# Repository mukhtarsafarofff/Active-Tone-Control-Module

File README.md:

(ENG) This electronic circuit consists of a network of filters which modify the signal before it is fed to speakers, headphones or recording devices by way of an amplifier. Tone control circuit  allows listeners to adjust sound to their liking and  the high-end of your tone. This enables the listener to customize the music output with either a high level of low frequency content through bass boost, or an increased level of high frequency content through a treble boost. The TL074 IC is a high-speed JFET input single operational amplifier.

(DEU) Diese elektronische Schaltung besteht aus einem Netzwerk von Filtern,die das Signal modifizieren, bevor es über einen Verstärker an Lautsprecher, Kopfhörer oder Aufnahmegeräte weitergeleitet wird. Mit der Klangregelungsschaltung können Zuhörer den Klang nach ihren Wünschen und den Höhen Ihres Tons anpassen.

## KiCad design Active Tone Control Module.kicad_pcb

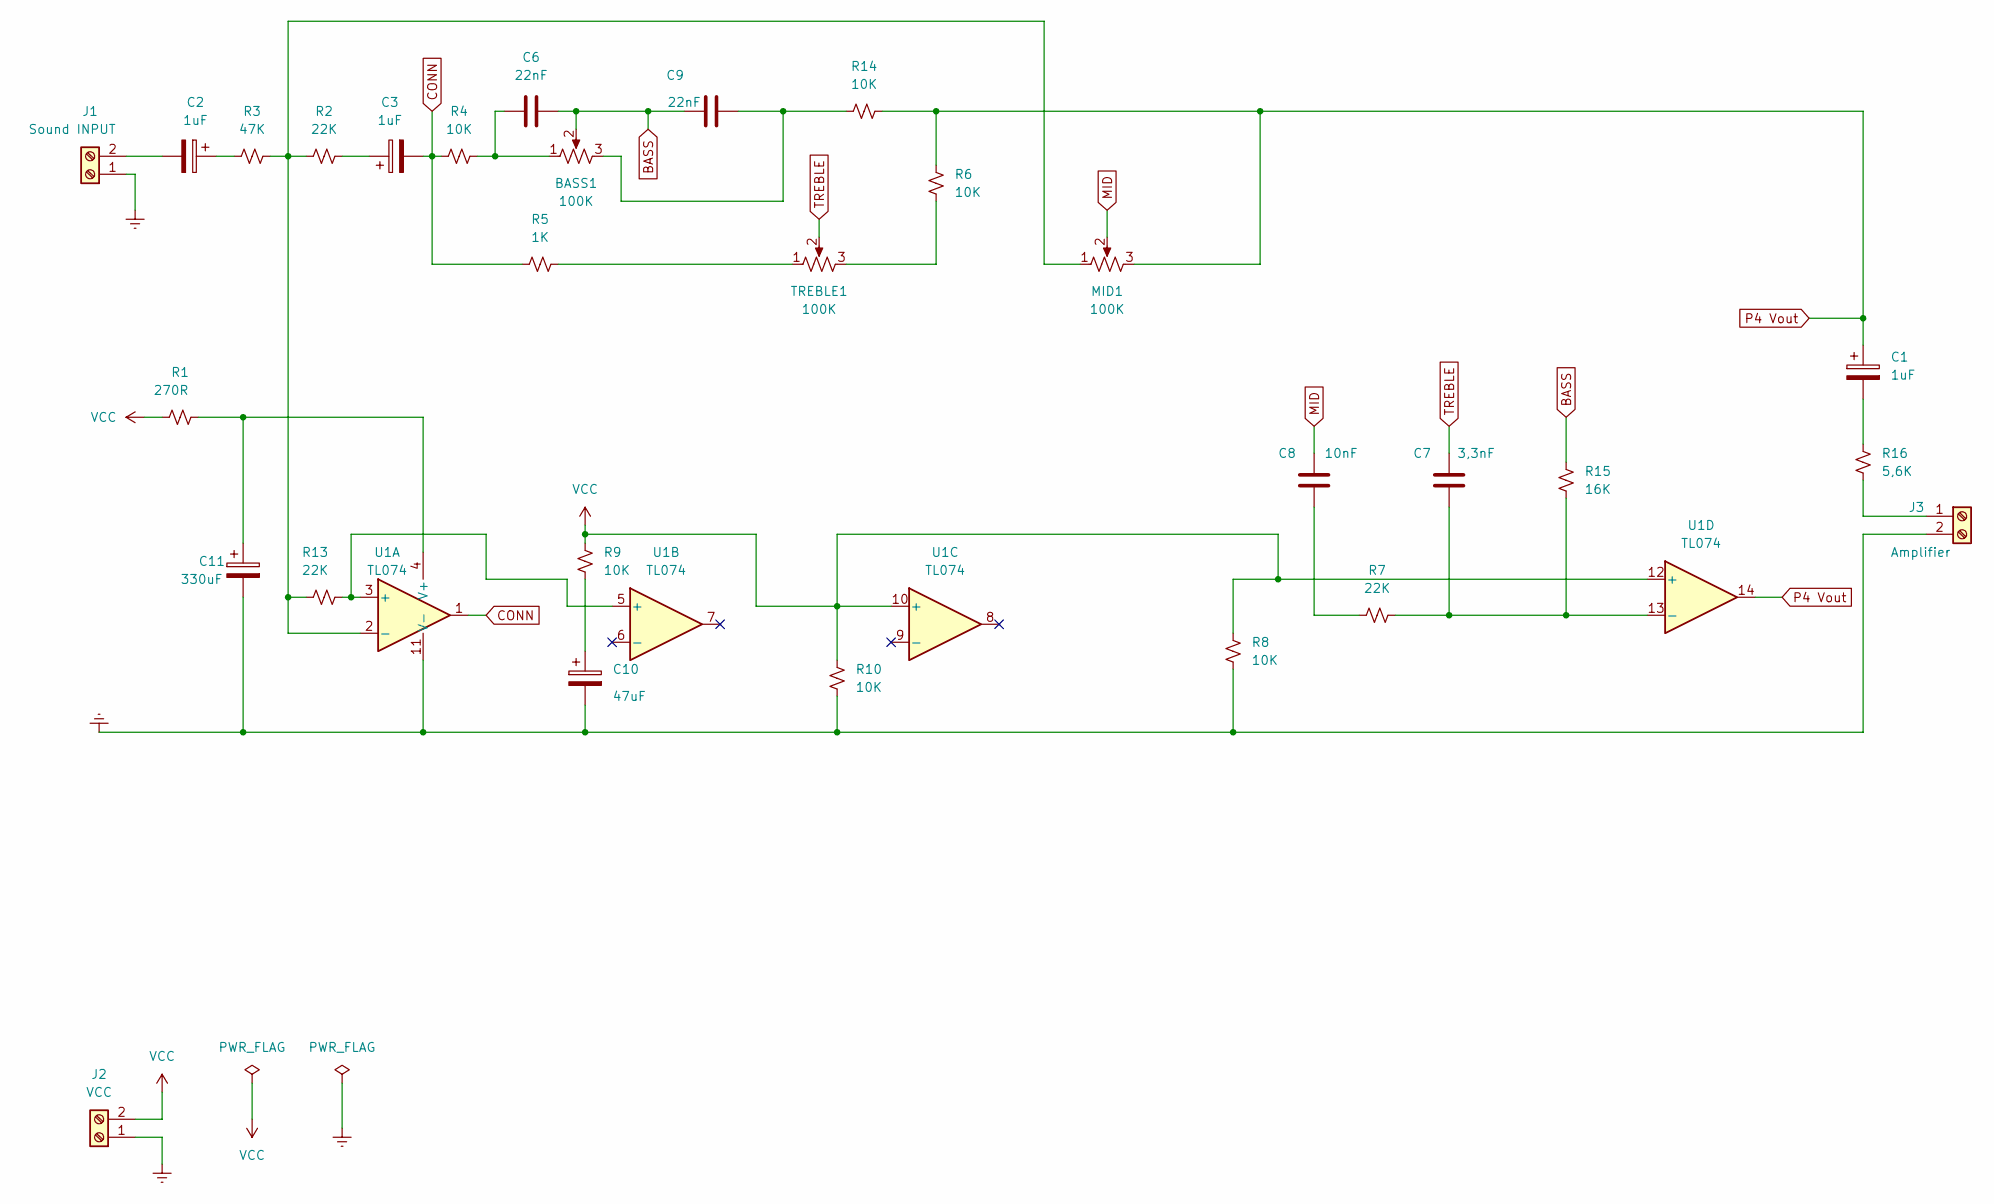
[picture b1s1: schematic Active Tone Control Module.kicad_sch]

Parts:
BASS1: 100K; Potentiometer_Vishay_148-149_Single_Horizontal
C1, C2, C3: 1uF; CP_Radial_D10.0mm_P7.50mm
C6, C9: 22nF; C_Disc_D7.5mm_W5.0mm_P7.50mm
C7: 3,3nF; C_Disc_D7.5mm_W5.0mm_P7.50mm
C8: 10nF; C_Disc_D7.5mm_W5.0mm_P7.50mm
C10: 47uF; CP_Radial_D10.0mm_P7.50mm
C11: 330uF; CP_Radial_D10.0mm_P7.50mm
J1: Sound INPUT; TerminalBlock_bornier-2_P5.08mm
J2: VCC; TerminalBlock_bornier-2_P5.08mm
J3: Amplifier; TerminalBlock_bornier-2_P5.08mm
MID1: 100K; Potentiometer_Vishay_148-149_Single_Horizontal
R1: 270R; R_Axial_DIN0414_L11.9mm_D4.5mm_P15.24mm_Horizontal
R2, R7, R13: 22K; R_Axial_DIN0414_L11.9mm_D4.5mm_P15.24mm_Horizontal
R3: 47K; R_Axial_DIN0414_L11.9mm_D4.5mm_P15.24mm_Horizontal
R4, R6, R8, R9, R10, R14: 10K; R_Axial_DIN0414_L11.9mm_D4.5mm_P15.24mm_Horizontal
R5: 1K; R_Axial_DIN0414_L11.9mm_D4.5mm_P15.24mm_Horizontal
R15: 16K; R_Axial_DIN0414_L11.9mm_D4.5mm_P15.24mm_Horizontal
R16: 5,6K; R_Axial_DIN0414_L11.9mm_D4.5mm_P15.24mm_Horizontal
TREBLE1: 100K; Potentiometer_Vishay_148-149_Single_Horizontal
U1: TL074; DIP-14_W7.62mm

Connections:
BASS: BASS1.2, C6.2, C9.1, R15.2
CONN: C3.2, R4.1, R5.1, U1.1
Earth: C10.2, C11.2, J1.1, J2.1, J3.2, R8.1, R10.1, U1.11 (V-)
MID: C8.2, MID1.2
unnamed: BASS1.1, C6.1, R4.2
unnamed: BASS1.3, C9.2, R14.1
unnamed: C1.2, R16.2
unnamed: C2.1, R3.1
unnamed: C3.1, R2.2
unnamed: C8.1, R7.1
unnamed: C10.1, R9.1
unnamed: C2.2, J1.2
unnamed: J3.1, R16.1
unnamed: R5.2, TREBLE1.1
unnamed: R6.1, TREBLE1.3
unnamed: R13.2, U1.3 (+), U1.5 (+)
unnamed: MID1.1, R2.1, R3.2, R13.1, U1.2 (-)
unnamed: C7.1, R7.2, R15.1, U1.13 (-)
unnamed: C11.1, R1.2, U1.4 (V+)
P4 Vout: C1.1, MID1.3, R6.2, R14.2, U1.14
TREBLE: C7.2, TREBLE1.2
VCC: J2.2, R1.1, R8.2, R9.2, R10.2, U1.10 (+), U1.12 (+)

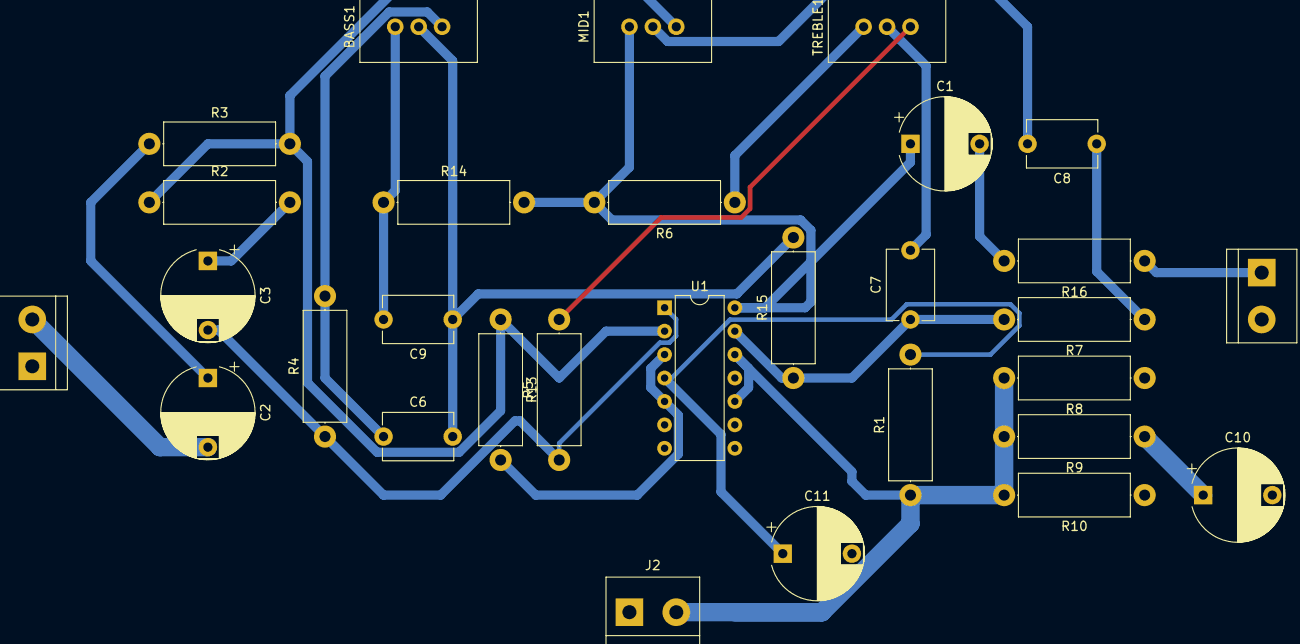
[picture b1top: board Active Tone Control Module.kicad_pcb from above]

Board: 2 copper layers, 30 parts (0 on the bottom side), 22 nets.

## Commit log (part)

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2024-03-22 Active Tone Control Module is accomplished
2024-03-23 Active Tone Control module is restored
2024-03-23 Tone control module is restored
